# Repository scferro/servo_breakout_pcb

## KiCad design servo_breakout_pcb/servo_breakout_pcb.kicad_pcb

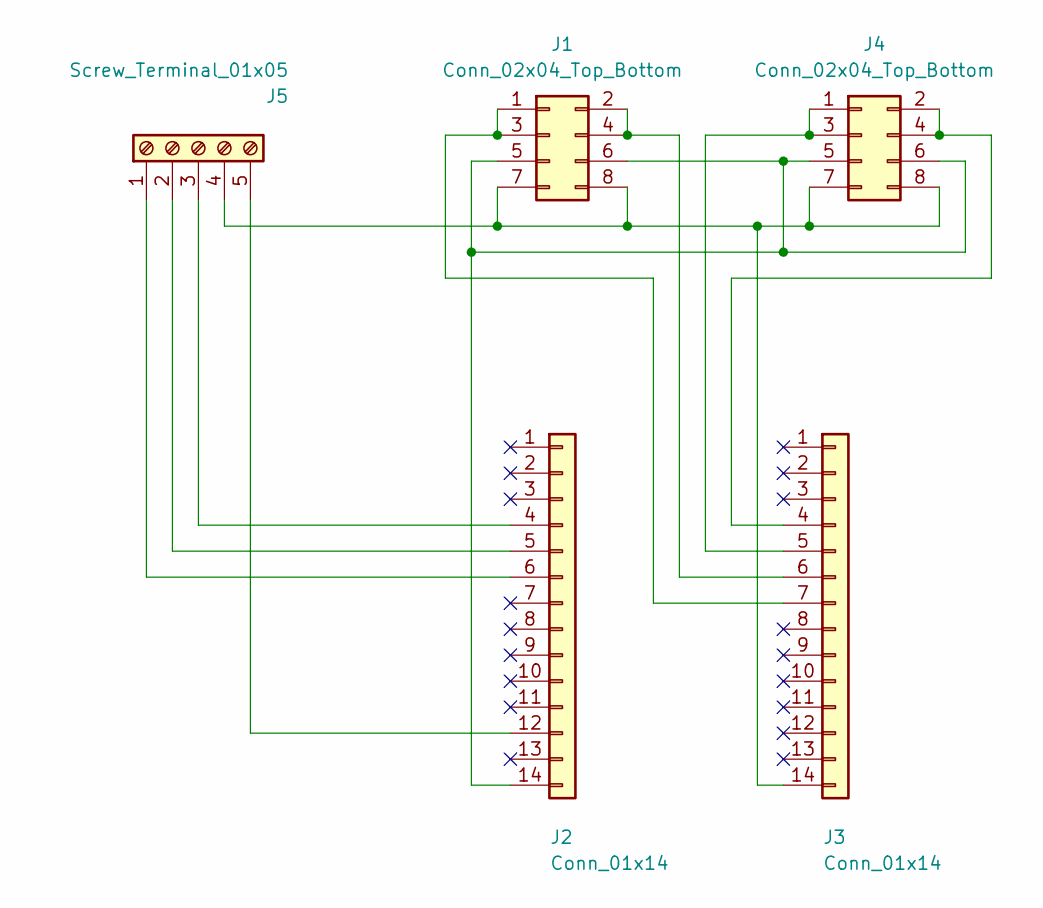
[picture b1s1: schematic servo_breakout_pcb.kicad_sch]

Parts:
J1, J4: Conn_02x04_Top_Bottom; PinHeader_2x04_P2.54mm_Vertical
J2, J3: Conn_01x14; PinSocket_1x14_P2.54mm_Vertical
J5: Screw_Terminal_01x05; TerminalBlock_bornier-5_P5.08mm

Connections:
unnamed: J1.1, J1.3, J3.7
unnamed: J1.2, J1.4, J3.6
unnamed: J2.4, J5.3
unnamed: J2.5, J5.2
unnamed: J2.6, J5.1
unnamed: J2.12, J5.5
unnamed: J3.5, J4.1, J4.3
unnamed: J3.4, J4.2, J4.4
unnamed: J1.5, J1.6, J2.14, J4.5, J4.6
unnamed: J1.7, J1.8, J3.14, J4.7, J4.8, J5.4

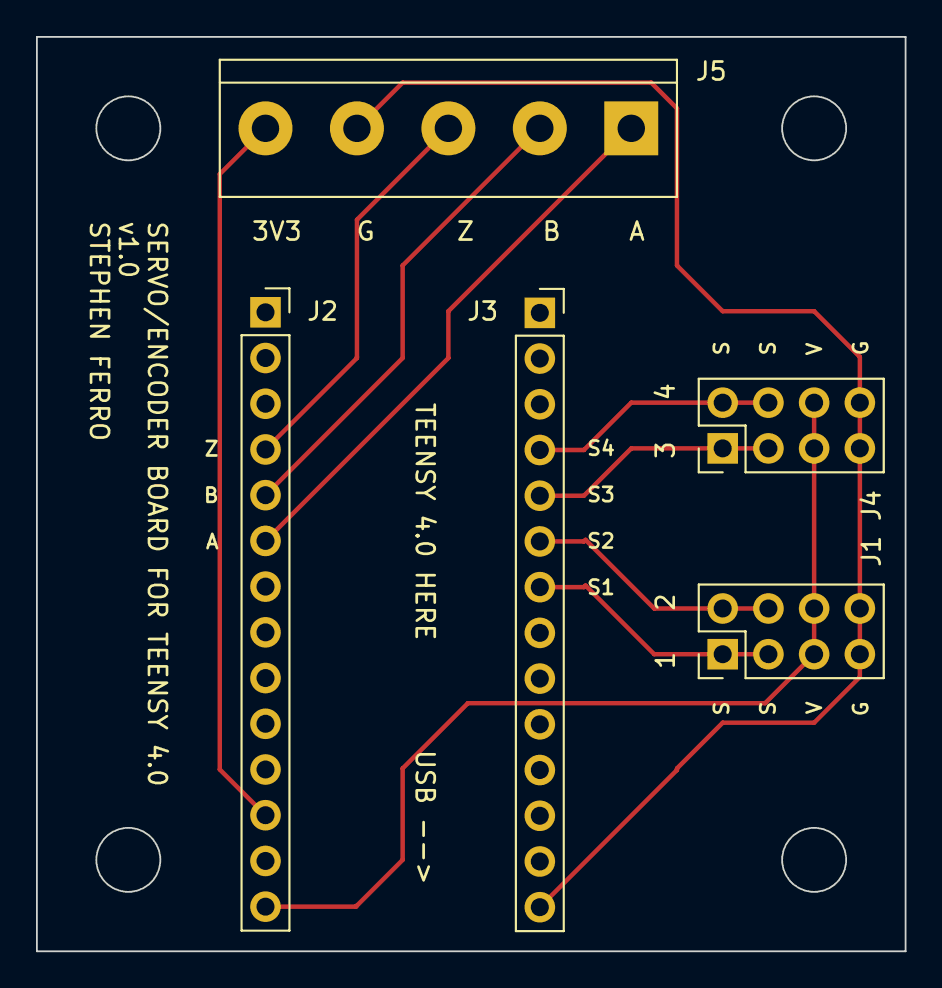
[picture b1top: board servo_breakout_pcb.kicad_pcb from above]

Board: 2 copper layers, 48.3 x 50.8 mm, 5 parts (0 on the bottom side), 10 nets.

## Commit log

2024-01-12 initial commit, created board for teensy
